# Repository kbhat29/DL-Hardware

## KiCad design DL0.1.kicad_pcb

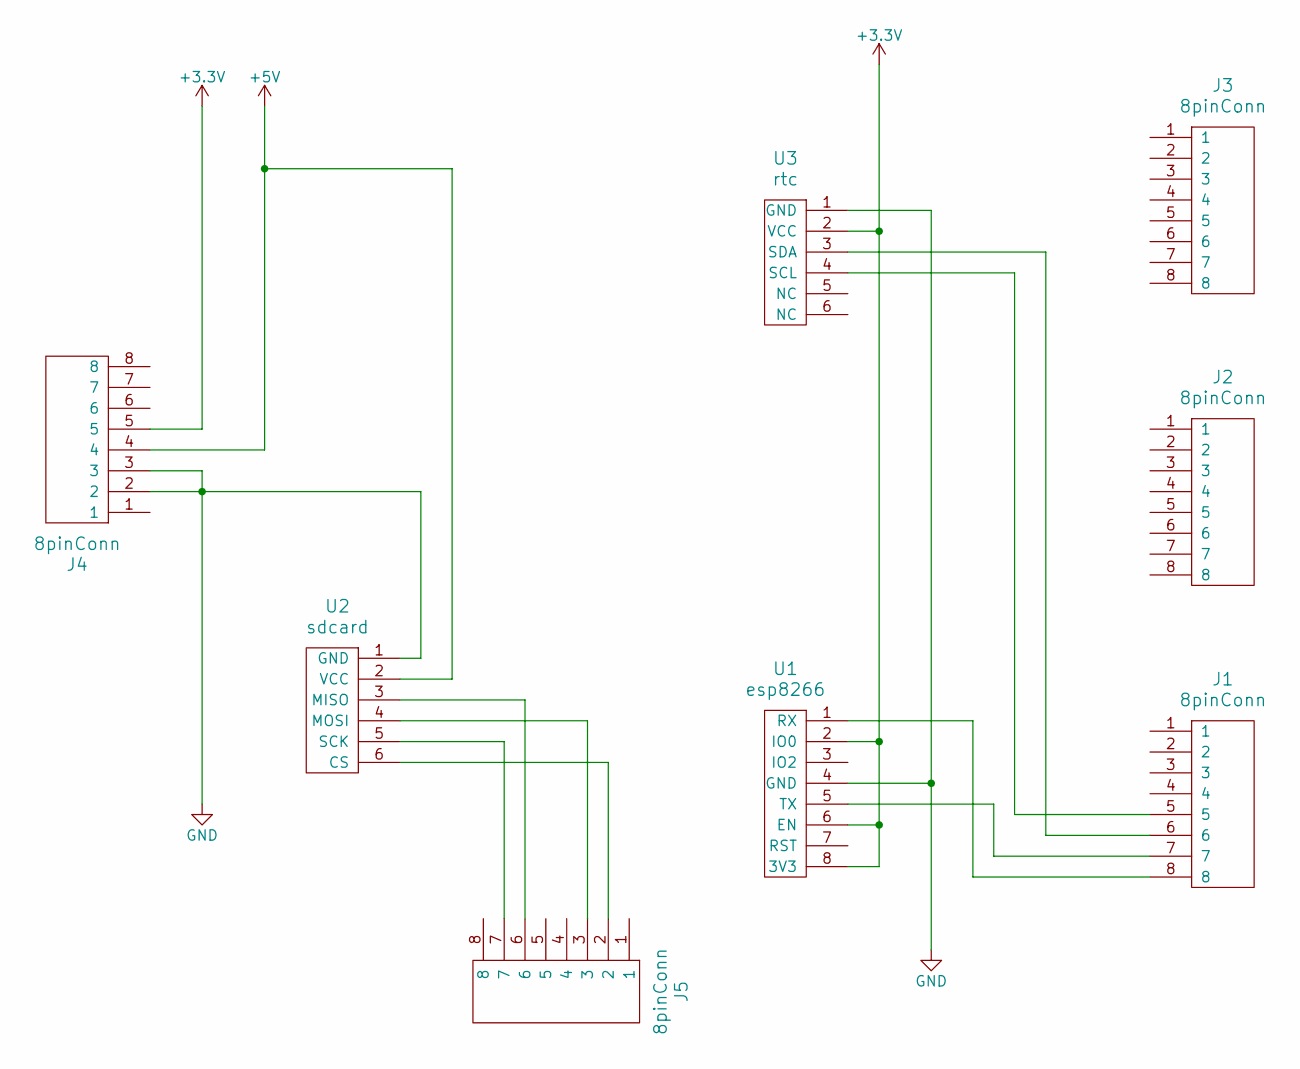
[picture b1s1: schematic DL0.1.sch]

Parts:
J1, J2, J3, J4: 8pinConn; 8pin_straight_conn
J5: 8pinConn; 8pin(4x4)_straight_conn
U1: esp8266; 8pin(4x4)_straight_conn
U2: sdcard; 6pin_right-angle_conn
U3: rtc; 6pin_right-angle_conn

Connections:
+3V3: J4.5, U1.2 (IO0), U1.6 (EN), U1.8 (3V3), U3.2 (VCC)
+5V: J4.4, U2.2 (VCC)
GND: J4.2, J4.3, U1.4 (GND), U2.1 (GND), U3.1 (GND)
unnamed: J1.5, U3.4 (SCL)
unnamed: J1.6, U3.3 (SDA)
unnamed: J1.7, U1.5 (TX)
unnamed: J1.8, U1.1 (RX)
unnamed: J5.2, U2.6 (CS)
unnamed: J5.3, U2.4 (MOSI)
unnamed: J5.6, U2.3 (MISO)
unnamed: J5.7, U2.5 (SCK)

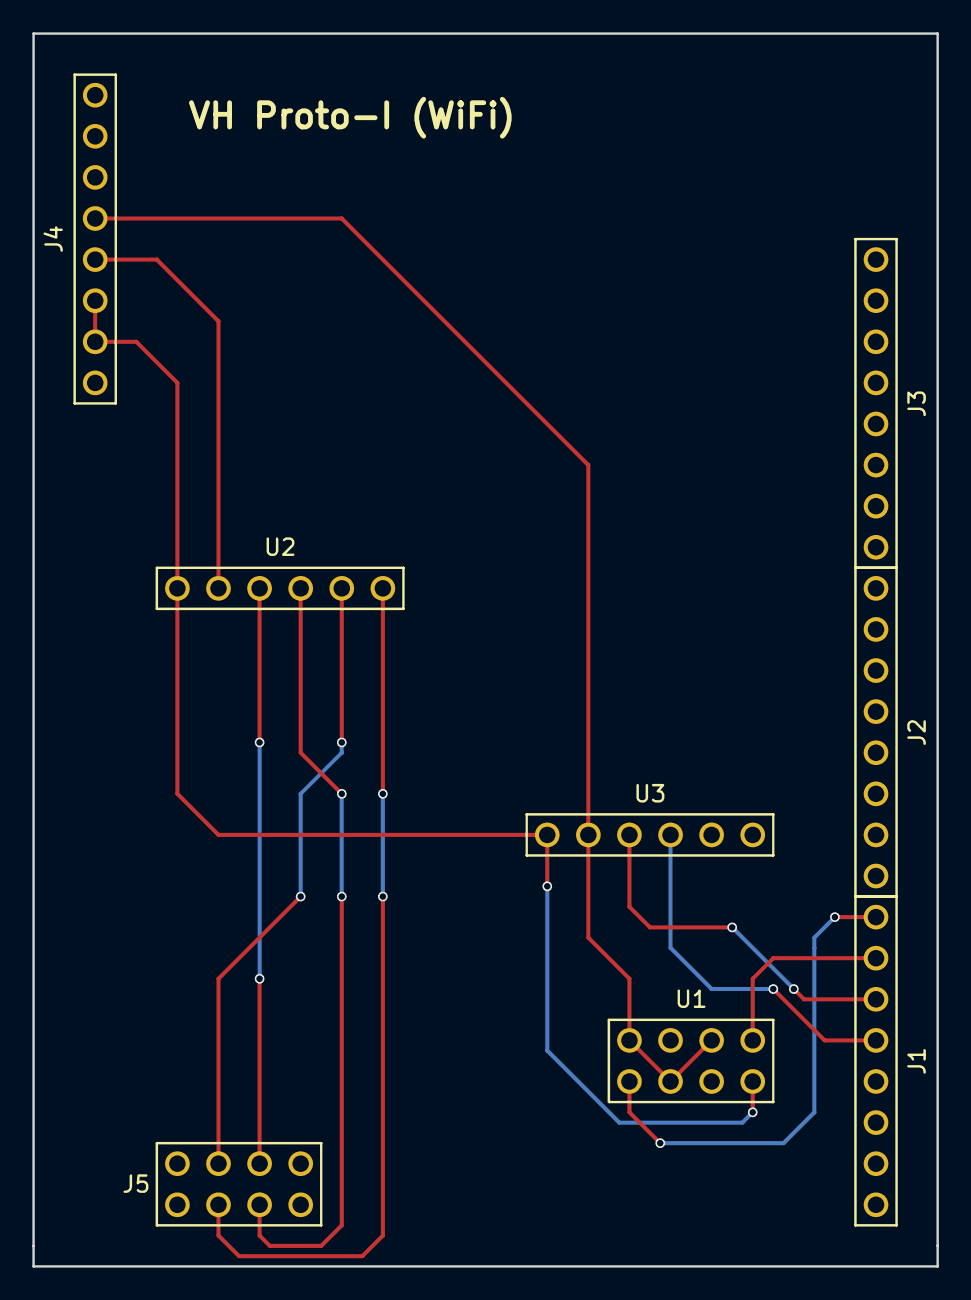
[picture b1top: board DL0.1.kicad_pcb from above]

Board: 2 copper layers, 55.9 x 76.2 mm, 8 parts (0 on the bottom side), 11 nets.

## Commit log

2018-01-03 dl hardware files
